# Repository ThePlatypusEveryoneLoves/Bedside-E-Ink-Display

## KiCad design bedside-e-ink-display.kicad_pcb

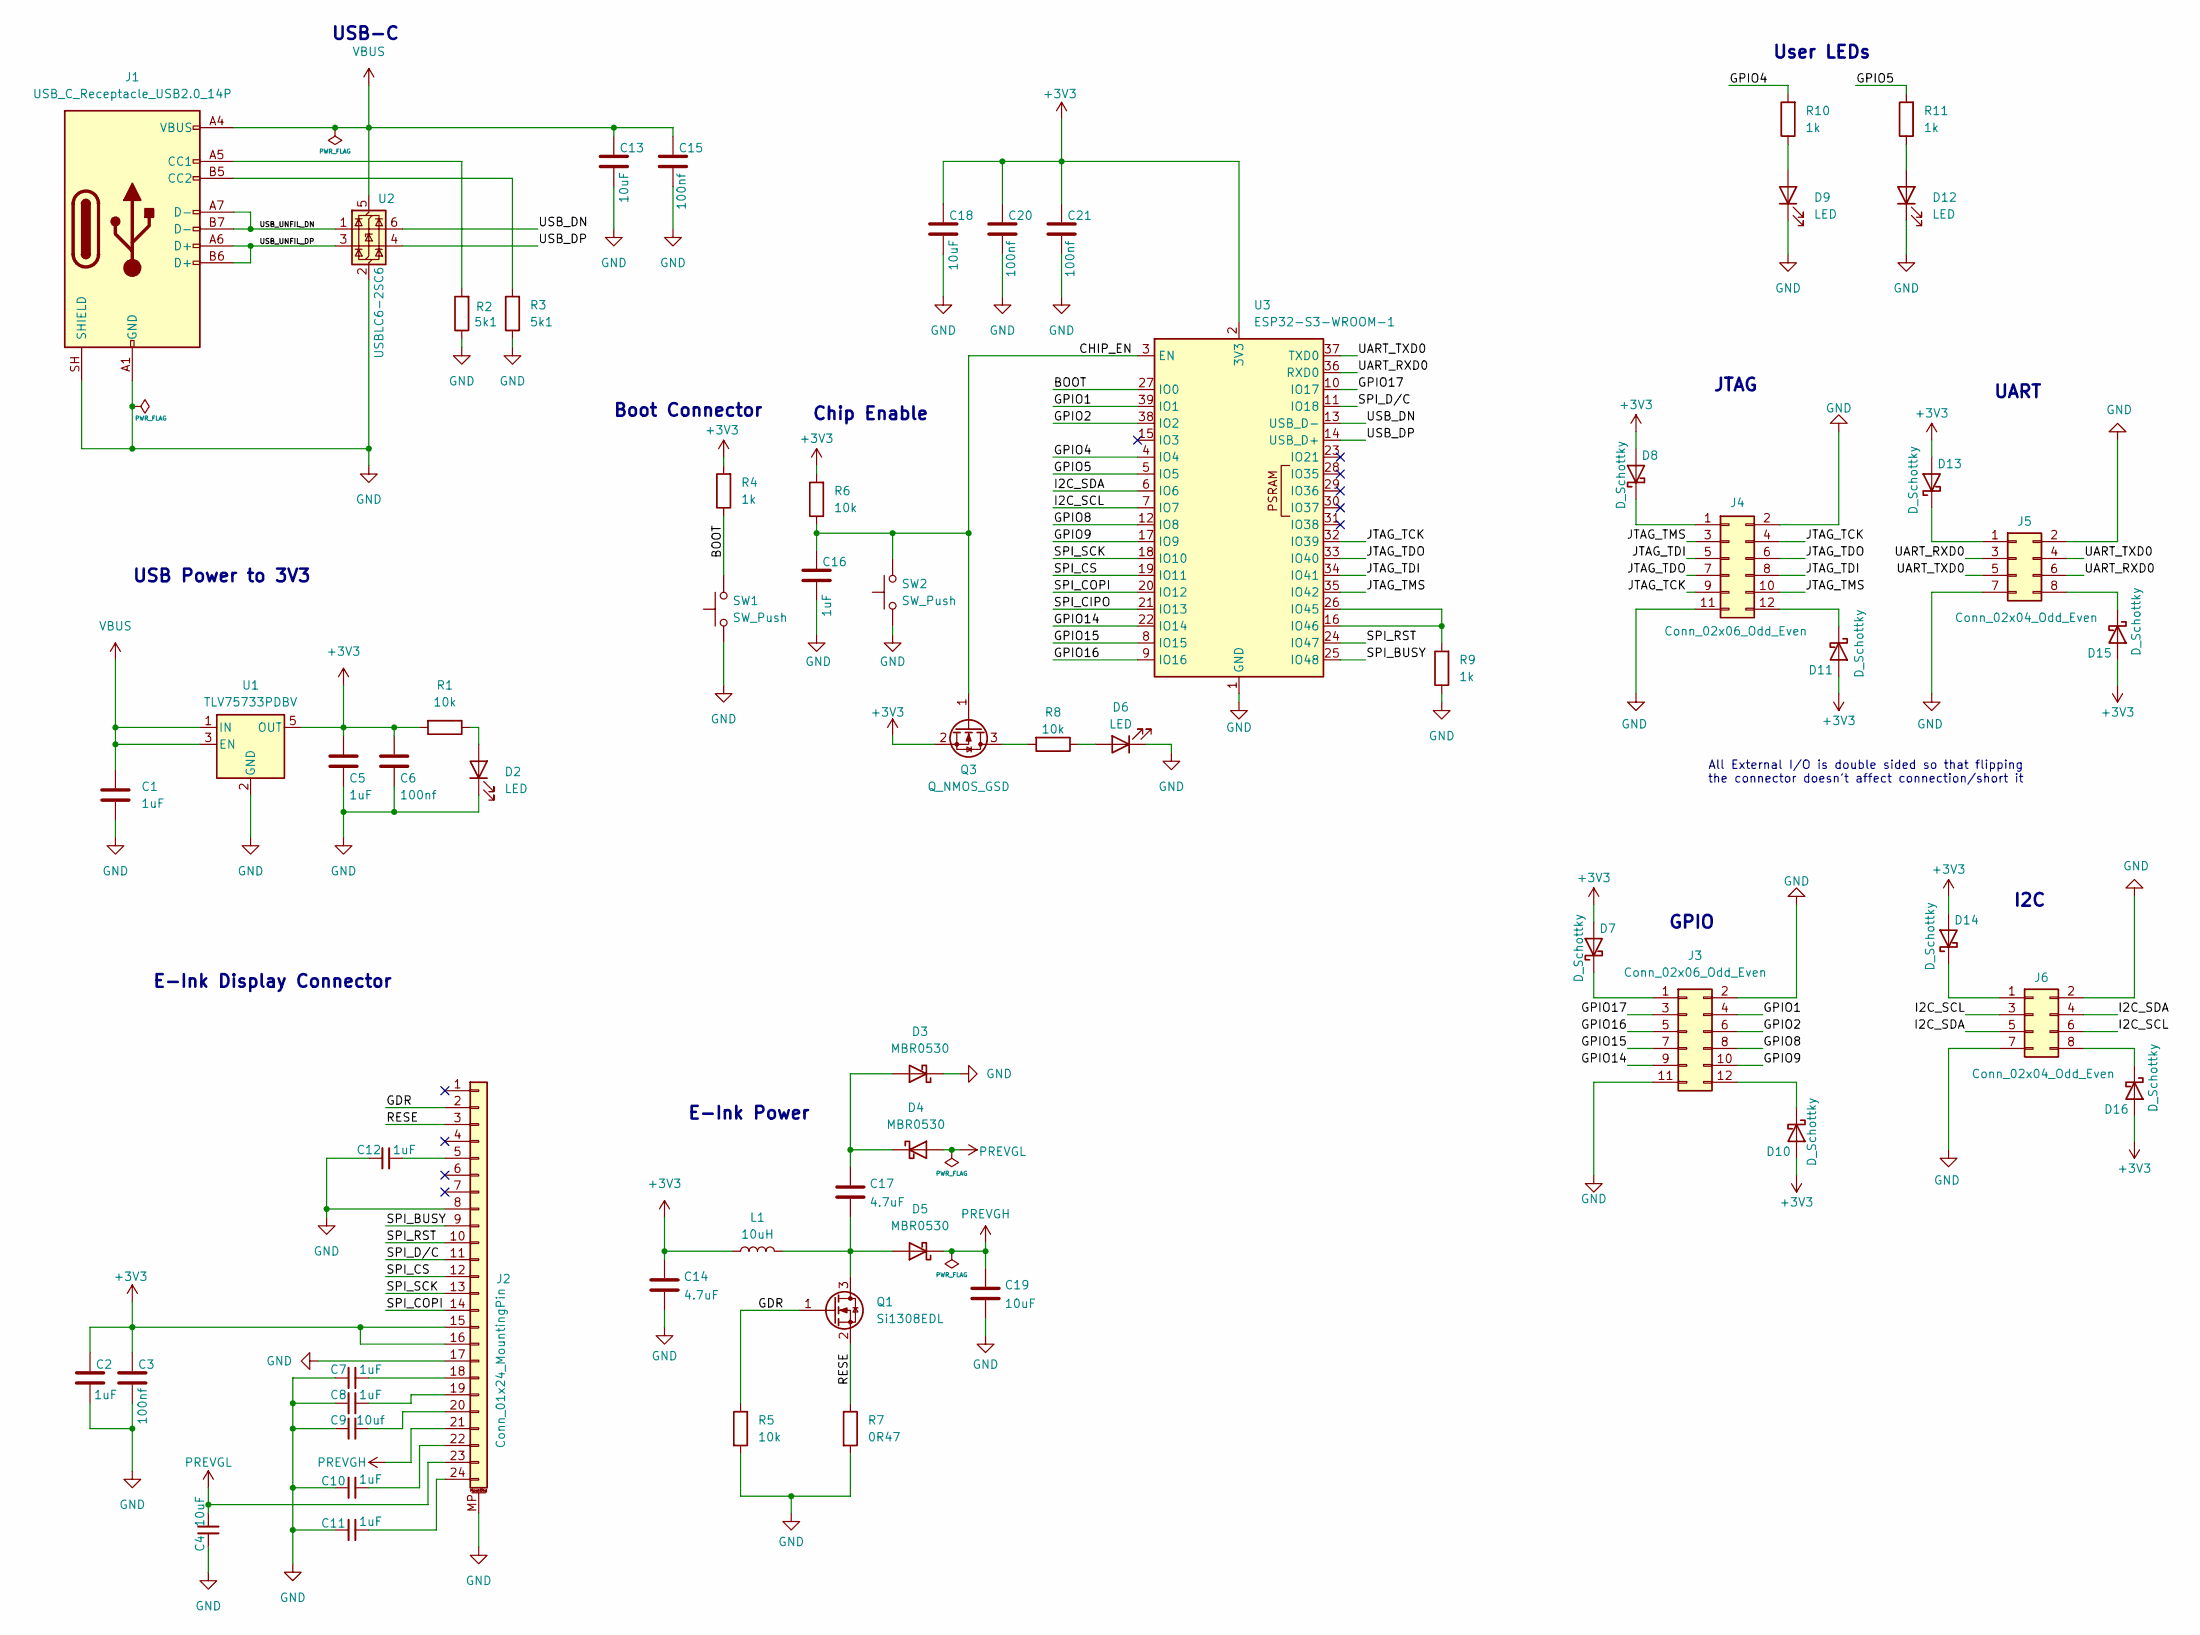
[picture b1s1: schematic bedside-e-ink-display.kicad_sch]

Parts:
C1: 1uF; C_0603_1608Metric; LCSC C15849
C2, C5, C7, C8, C10, C11, C12, C16: 1uF; C_0603_1608Metric; LCSC C1592
C3, C6, C15, C20, C21: 100nf; C_0603_1608Metric
C4, C13, C18, C19: 10uF; C_0603_1608Metric
C9: 10uf; C_0603_1608Metric
C14, C17: 4.7uF; C_0603_1608Metric
D2, D6, D9, D12: LED; LED_0805_2012Metric
D3, D4, D5: MBR0530; D_SOD-123
D7, D8, D10, D11, D13, D14, D15, D16: D_Schottky; D_SOD-323
J1: USB_C_Receptacle_USB2.0_14P; USB_C_Receptacle_GCT_USB4085
J2: Conn_01x24_MountingPin; Hirose_FH12-24S-0.5SH_1x24-1MP_P0.50mm_Horizontal
J3, J4: Conn_02x06_Odd_Even; PinHeader_2x06_P2.54mm_Horizontal
J5, J6: Conn_02x04_Odd_Even; PinHeader_2x04_P2.00mm_Horizontal
L1: 10uH; L_Vishay_IHLP-2525
Q1: Si1308EDL; SOT-323_SC-70
Q3: Q_NMOS_GSD; SOT-23
R1, R5, R6, R8: 10k; R_0603_1608Metric
R2, R3: 5k1; R_0603_1608Metric
R4, R9, R10, R11: 1k; R_0603_1608Metric
R7: 0R47; R_0603_1608Metric
SW1, SW2: SW_Push; SW_Push_SPST_NO_Alps_SKRK
U1: TLV75733PDBV; SOT-23-5
U2: USBLC6-2SC6; SOT-23-6
U3: ESP32-S3-WROOM-1

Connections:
+3V3: C2.1, C3.1, C5.1, C6.1, C14.1, C18.1, C20.1, C21.1, D7.2 (A), D8.2 (A), D10.2 (A), D11.2 (A), D13.2 (A), D14.2 (A), D15.2 (A), D16.2 (A), J2.15, J2.16, L1.1, Q3.2 (S), R1.2, R4.2, R6.2, U1.5 (OUT), U3.2 (3V3)
/BOOT: R4.1, SW1.2, U3.27 (IO0)
/CHIP_EN: C16.1, Q3.1 (G), R6.1, SW2.2, U3.3 (EN)
/GDR: J2.2, Q1.1 (G), R5.1
/GPIO1: J3.4, U3.39 (IO1)
/GPIO2: J3.6, U3.38 (IO2)
/GPIO4: R10.2, U3.4 (IO4)
/GPIO5: R11.2, U3.5 (IO5)
/GPIO8: J3.8, U3.12 (IO8)
/GPIO9: J3.10, U3.17 (IO9)
/GPIO14: J3.9, U3.22 (IO14)
/GPIO15: J3.7, U3.8 (IO15)
/GPIO16: J3.5, U3.9 (IO16)
/GPIO17: J3.3, U3.10 (IO17)
/I2C_SCL: J6.3, J6.6, U3.7 (IO7)
/I2C_SDA: J6.4, J6.5, U3.6 (IO6)
/JTAG_TCK: J4.4, J4.9, U3.32 (IO39)
/JTAG_TDI: J4.5, J4.8, U3.34 (IO41)
/JTAG_TDO: J4.6, J4.7, U3.33 (IO40)
/JTAG_TMS: J4.3, J4.10, U3.35 (IO42)
/RESE: J2.3, Q1.2 (S), R7.1
/SPI_BUSY: J2.9, U3.25 (IO48)
/SPI_CIPO: U3.21 (IO13)
/SPI_COPI: J2.14, U3.20 (IO12)
/SPI_CS: J2.12, U3.19 (IO11)
/SPI_D/C: J2.11, U3.11 (IO18)
/SPI_RST: J2.10, U3.24 (IO47)
/SPI_SCK: J2.13, U3.18 (IO10)
/UART_RXD0: J5.3, J5.6, U3.36 (RXD0)
/UART_TXD0: J5.4, J5.5, U3.37 (TXD0)
/USB_DN: U2.6 (I/O1), U3.13 (USB_D-)
/USB_DP: U2.4 (I/O2), U3.14 (USB_D+)
/USB_UNFIL_DN: J1.A7 (D-), J1.B7 (D-), U2.1 (I/O1)
/USB_UNFIL_DP: J1.A6 (D+), J1.B6 (D+), U2.3 (I/O2)
GND: C1.2, C2.2, C3.2, C4.1, C5.2, C6.2, C7.1, C8.1, C9.1, C10.1, C11.1, C12.1, C13.2, C14.2, C15.2, C16.2, C18.2, C19.2, C20.2, C21.2, D2.1 (K), D3.1 (K), D6.1 (K), D9.1 (K), D12.1 (K), J1.A1 (GND), J1.A12 (GND), J1.B1 (GND), J1.B12 (GND), J1.SH (SHIELD), J2.8, J2.17, J2.MP (MountPin), J3.2, J3.11, J4.2, J4.11, J5.2, J5.7, J6.2, J6.7, R2.1, R3.1, R5.2, R7.2, R9.1, SW1.1, SW2.1, U1.2 (GND), U2.2 (GND), U3.1 (GND), U3.40 (GND), U3.41 (GND)
unnamed: D2.2 (A), R1.1
unnamed: C17.1, D3.2 (A), D4.1 (K)
unnamed: C17.2, D5.2 (A), L1.2, Q1.3 (D)
unnamed: D6.2 (A), R8.1
unnamed: D7.1 (K), J3.1
unnamed: D8.1 (K), J4.1
unnamed: D9.2 (A), R10.1
unnamed: D10.1 (K), J3.12
unnamed: D11.1 (K), J4.12
unnamed: D12.2 (A), R11.1
unnamed: D13.1 (K), J5.1
unnamed: D14.1 (K), J6.1
unnamed: D15.1 (K), J5.8
unnamed: D16.1 (K), J6.8
unnamed: J1.A5 (CC1), R2.2
unnamed: J1.B5 (CC2), R3.2
unnamed: C12.2, J2.5
unnamed: C7.2, J2.18
unnamed: C8.2, J2.19
unnamed: C9.2, J2.20
unnamed: C10.2, J2.22
unnamed: C11.2, J2.24
unnamed: Q3.3 (D), R8.2
unnamed: R9.2, U3.16 (IO46), U3.26 (IO45)
PREVGH: C19.1, D5.1 (K), J2.21
PREVGL: C4.2, D4.2 (A), J2.23
VBUS: C1.1, C13.1, C15.1, J1.A4 (VBUS), J1.A9 (VBUS), J1.B4 (VBUS), J1.B9 (VBUS), U1.1 (IN), U1.3 (EN), U2.5 (VBUS)

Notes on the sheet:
Boot Connector
USB Power to 3V3
E-Ink Power
I2C
E-Ink Display Connector
User LEDs
JTAG
UART
Chip Enable
GPIO
All External I/O is double sided so that flipping the connector doesn't affect connection/short it
USB-C

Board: 2 copper layers, 61 parts (0 on the bottom side), 61 nets, no tracks yet.
